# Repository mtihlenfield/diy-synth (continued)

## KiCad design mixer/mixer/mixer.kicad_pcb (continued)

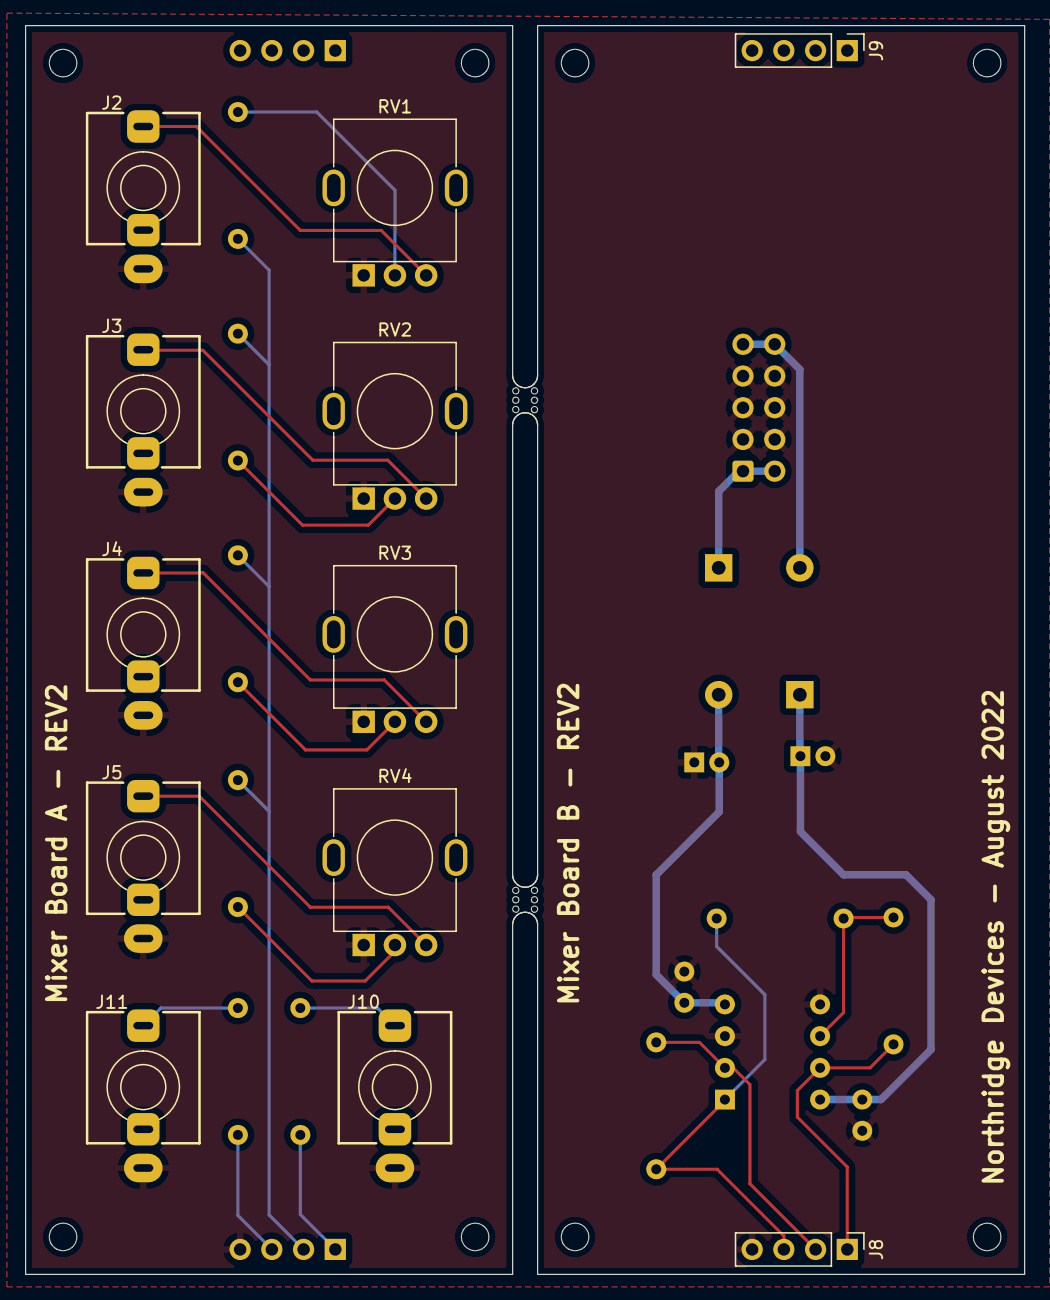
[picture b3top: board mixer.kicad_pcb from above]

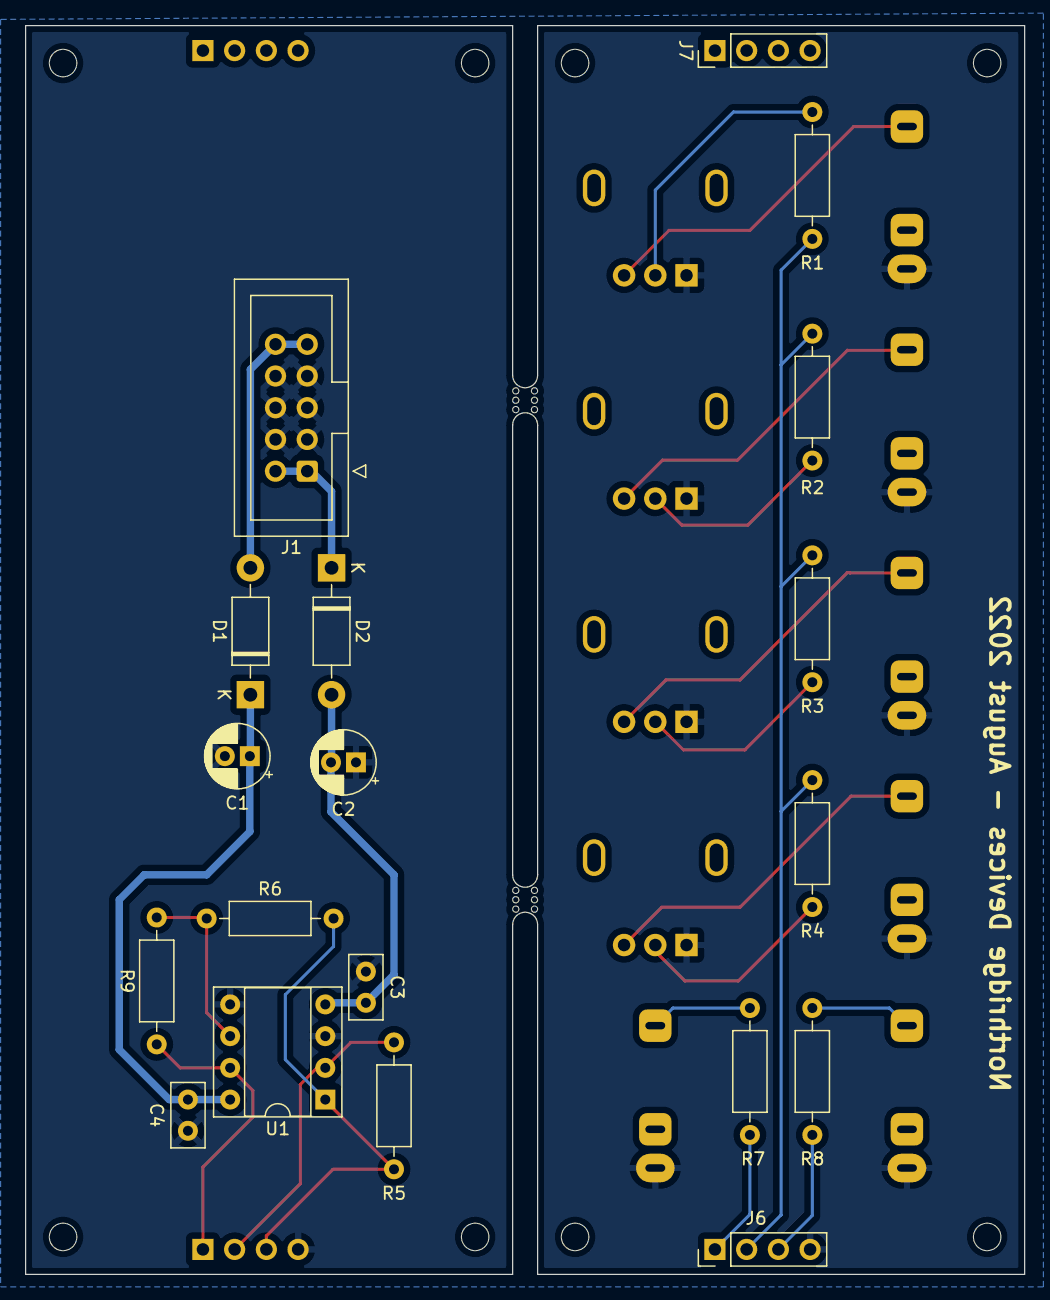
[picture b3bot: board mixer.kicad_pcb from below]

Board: 2 copper layers, 80.0 x 100.0 mm, 41 parts (19 on the bottom side), 22 nets.

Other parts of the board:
mouse-bite-2mm-slot, mouse-bite-2mm-slot#2: VAL**; mouse-bite-2mm-slot

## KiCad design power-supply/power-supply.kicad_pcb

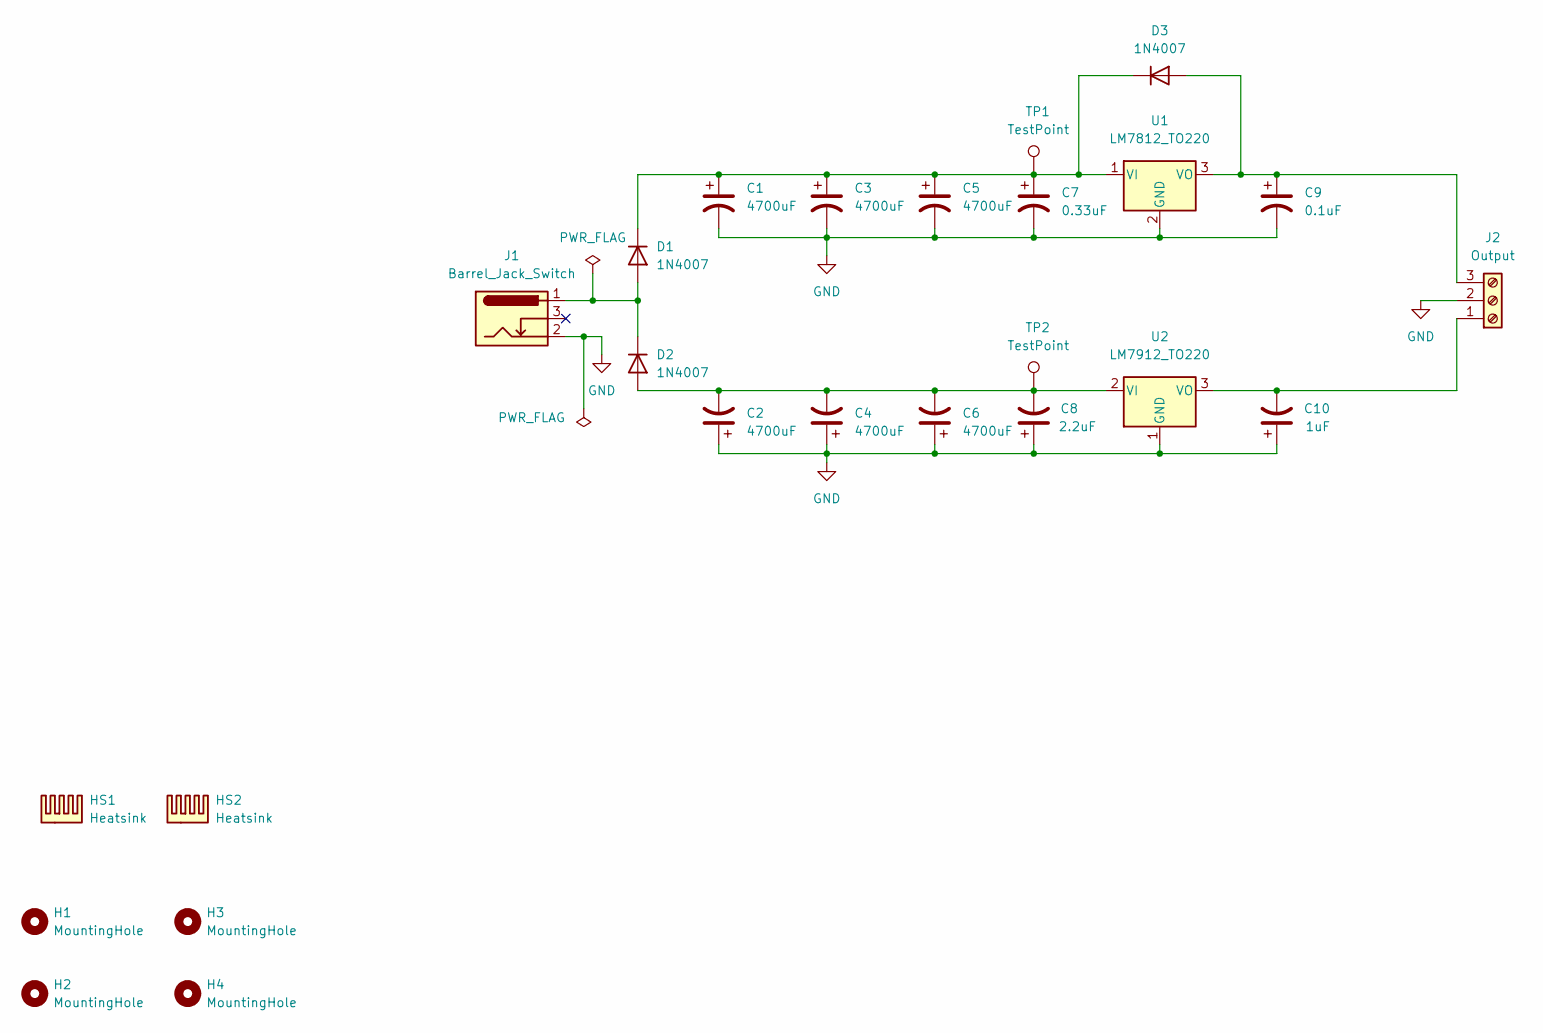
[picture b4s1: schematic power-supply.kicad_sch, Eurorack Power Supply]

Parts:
C1, C2, C3, C4, C5, C6: 4700uF; CP_Radial_D16.0mm_P7.50mm; Manufacturer Part No. JRB1E472M07501600250000B
C7: 0.33uF; CP_Radial_Tantal_D5.0mm_P2.50mm; Manufacturer Part No. 1uF 35V Radial Capacitor Tantalum
C8: 2.2uF; CP_Radial_Tantal_D5.0mm_P2.50mm; Manufacturer Part No. 1uF 35V Radial Capacitor Tantalum
C9: 0.1uF; CP_Radial_Tantal_D5.0mm_P2.50mm; Manufacturer Part No. 1uF 35V Radial Capacitor Tantalum
C10: 1uF; CP_Radial_Tantal_D5.0mm_P2.50mm; Manufacturer Part No. 1uF 35V Radial Capacitor Tantalum
D1, D2, D3: 1N4007; D_DO-41_SOD81_P10.16mm_Horizontal; Manufacturer Part No. 1N4007
H1, H2, H3, H4: MountingHole; MountingHole_3.2mm_M3
HS1, HS2: Heatsink; Manufacturer Part No. Tayda
J1: Barrel_Jack_Switch; BarrelJack_Horizontal_2.1mm_WEALTH_METAL; Manufacturer Part No. DC Power Jack 2.1mm
J2: Output; DG126; Manufacturer Part No. DG126-03P
TP1, TP2: TestPoint; TestPoint_Pad_D1.5mm
U1: LM7812_TO220; TO-220-3_Vertical; Manufacturer Part No. L7812CV
U2: LM7912_TO220; TO-220-3_Vertical; Manufacturer Part No. L7912CV

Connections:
GND: C1.2, C2.1, C3.2, C4.1, C5.2, C6.1, C7.2, C8.1, C9.2, C10.1, J1.2, J2.2, U1.2 (GND), U2.1 (GND)
unnamed: C1.1, C3.1, C5.1, C7.1, D1.1 (K), D3.1 (K), TP1.1, U1.1 (VI)
unnamed: C2.2, C4.2, C6.2, C8.2, D2.2 (A), TP2.1, U2.2 (VI)
unnamed: C9.1, D3.2 (A), J2.3, U1.3 (VO)
unnamed: C10.2, J2.1, U2.3 (VO)
unnamed: D1.2 (A), D2.1 (K), J1.1

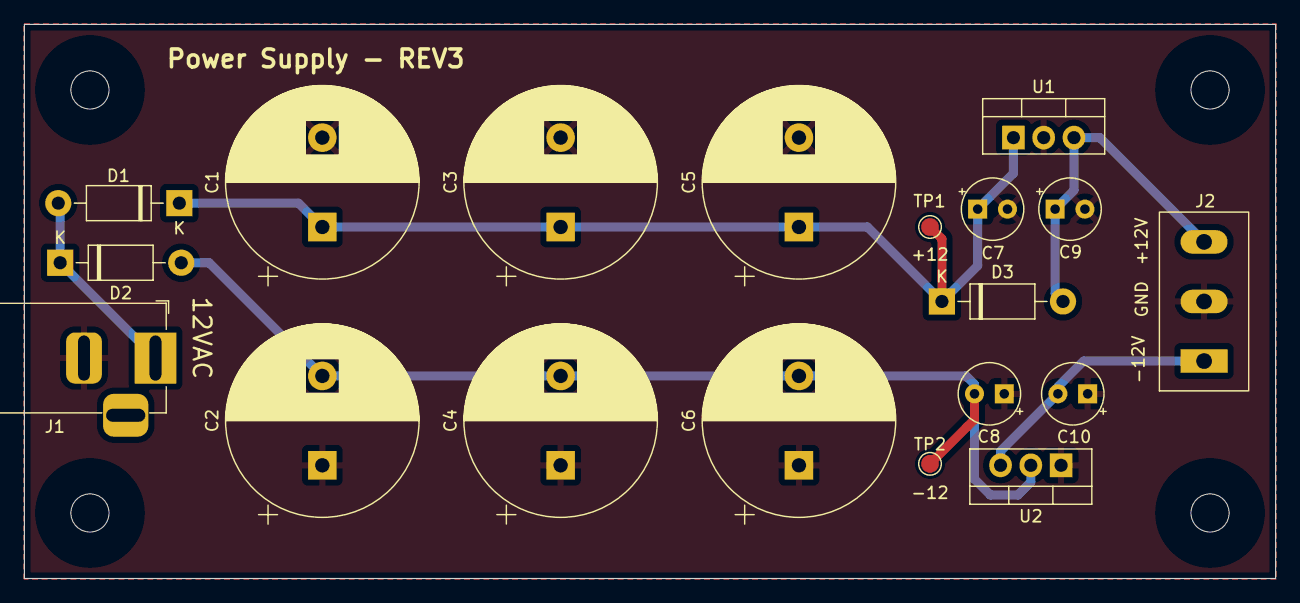
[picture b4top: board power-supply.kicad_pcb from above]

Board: 2 copper layers, 105.0 x 46.5 mm, 23 parts (0 on the bottom side), 6 nets.

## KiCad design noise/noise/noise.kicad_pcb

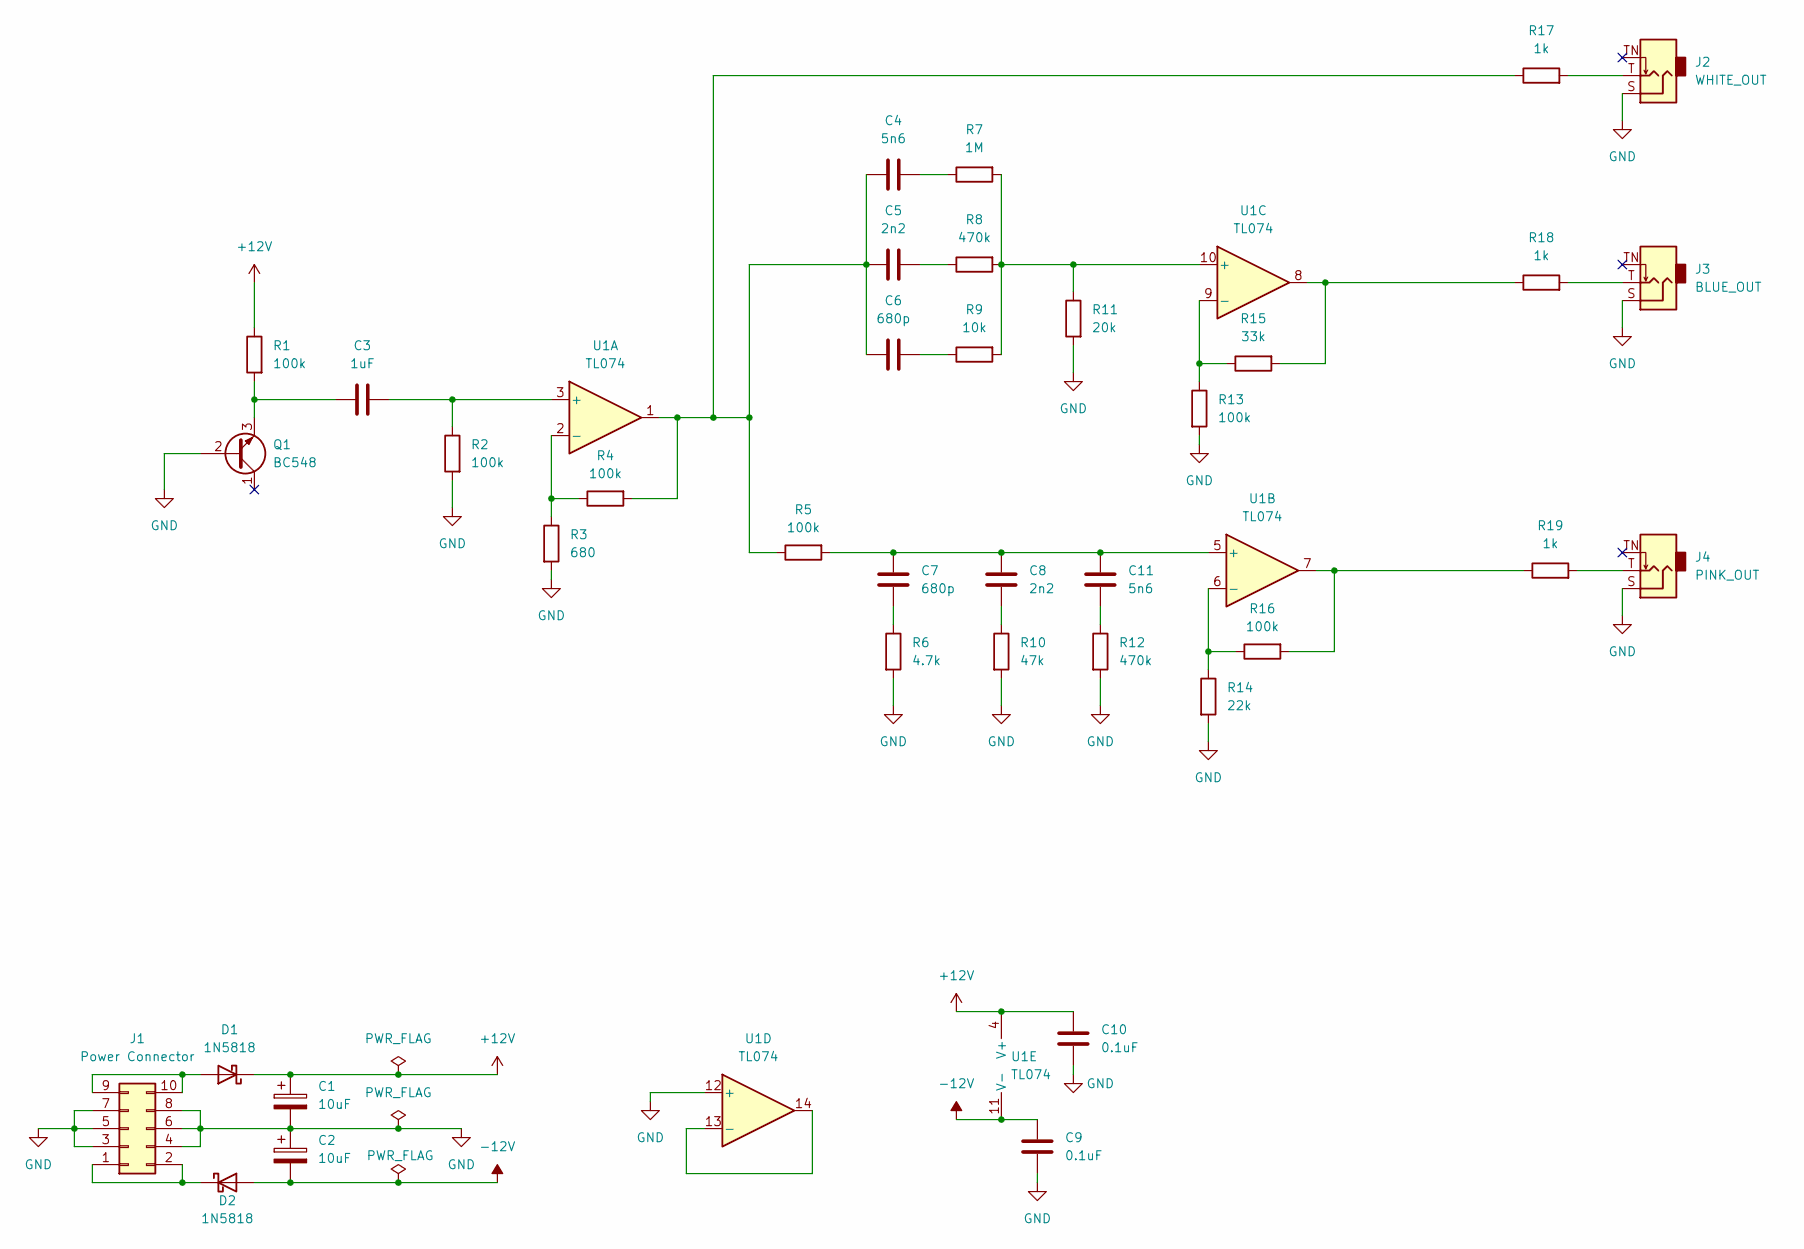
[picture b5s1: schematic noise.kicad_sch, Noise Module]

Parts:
C1, C2: 10uF; CP_Radial_D5.0mm_P2.00mm; Manufacturer Part No. WK1CM100D11OT
C3: 1uF; C_Rect_L7.2mm_W3.5mm_P5.00mm_FKS2_FKP2_MKS2_MKP2; Manufacturer Part No. MKS2B041001C00KSSD
C4, C11: 5n6; C_Rect_L7.2mm_W2.5mm_P5.00mm_FKS2_FKP2_MKS2_MKP2; Manufacturer Part No. 5.6nF/100V
C5, C8: 2n2; C_Rect_L7.2mm_W2.5mm_P5.00mm_FKS2_FKP2_MKS2_MKP2; Manufacturer Part No. FKS2D012201A00JSSD
C6, C7: 680p; C_Rect_L7.2mm_W5.5mm_P5.00mm_FKS2_FKP2_MKS2_MKP2; Manufacturer Part No. FKP2O106801G00JSSD
C9, C10: 0.1uF; C_Disc_D5.0mm_W2.5mm_P2.50mm; Manufacturer Part No. 0.1uF 50V Ceramic Disc Capacitor
D1, D2: 1N5818; D_DO-41_SOD81_P10.16mm_Horizontal; Manufacturer Part No. 1N5817
J1: Power Connector; IDC-Header_2x05_P2.54mm_Vertical; Manufacturer Part No. BHD10PHZT
J2: WHITE_OUT; PJ-323M; Manufacturer Part No. PJ-323M
J3: BLUE_OUT; PJ-323M; Manufacturer Part No. PJ-323M
J4: PINK_OUT; PJ-323M; Manufacturer Part No. PJ-323M
Q1: BC548; TO-92_Inline; Manufacturer Part No. BC548B
R1, R2, R4, R5, R13, R16: 100k; R_Axial_DIN0207_L6.3mm_D2.5mm_P10.16mm_Horizontal; Manufacturer Part No. MF0W4FF1003A50
R3: 680; R_Axial_DIN0207_L6.3mm_D2.5mm_P10.16mm_Horizontal; Manufacturer Part No. MF0W4FF6800A50
R6: 4.7k; R_Axial_DIN0207_L6.3mm_D2.5mm_P10.16mm_Horizontal; Manufacturer Part No. MF0W4FF4701A50
R7: 1M; R_Axial_DIN0207_L6.3mm_D2.5mm_P10.16mm_Horizontal; Manufacturer Part No. MF0W4FF1004A50
R8, R12: 470k; R_Axial_DIN0207_L6.3mm_D2.5mm_P10.16mm_Horizontal; Manufacturer Part No. MF0W4FF4703A50
R9: 10k; R_Axial_DIN0207_L6.3mm_D2.5mm_P10.16mm_Horizontal; Manufacturer Part No. MF0W4FF1002A50
R10: 47k; R_Axial_DIN0207_L6.3mm_D2.5mm_P10.16mm_Horizontal; Manufacturer Part No. MF0W4FF4702A50
R11: 20k; R_Axial_DIN0207_L6.3mm_D2.5mm_P10.16mm_Horizontal; Manufacturer Part No. MF0W4FF2002A50
R14: 22k; R_Axial_DIN0207_L6.3mm_D2.5mm_P10.16mm_Horizontal; Manufacturer Part No. MF0W4FF2202A50
R15: 33k; R_Axial_DIN0207_L6.3mm_D2.5mm_P10.16mm_Horizontal; Manufacturer Part No. MF0W4FF3302A50
R17, R18, R19: 1k; R_Axial_DIN0207_L6.3mm_D2.5mm_P10.16mm_Horizontal; Manufacturer Part No. MF0W4FF1001A50
U1: TL074; DIP-14_W7.62mm_Socket; Manufacturer Part No. TL074CN

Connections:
+12V: C1.1, C10.1, D1.1 (K), R1.1, U1.4 (V+)
-12V: C2.2, C9.1, D2.2 (A), U1.11 (V-)
GND: C1.2, C2.1, C9.2, C10.2, J1.3, J1.4, J1.5, J1.6, J1.7, J1.8, J2.S, J3.S, J4.S, Q1.2 (B), R2.2, R3.2, R6.2, R10.2, R11.2, R12.2, R13.2, R14.2, U1.12 (+)
unnamed: C3.1, Q1.3 (E), R1.2
unnamed: C3.2, R2.1, U1.3 (+)
unnamed: C4.1, C5.1, C6.1, R4.2, R5.1, R17.1, U1.1
unnamed: C4.2, R7.1
unnamed: C5.2, R8.1
unnamed: C6.2, R9.1
unnamed: C7.1, R6.1
unnamed: C8.1, R10.1
unnamed: C11.1, R12.1
unnamed: C7.2, C8.2, C11.2, R5.2, U1.5 (+)
unnamed: D1.2 (A), J1.9, J1.10
unnamed: D2.1 (K), J1.1, J1.2
unnamed: J2.T, R17.2
unnamed: J3.T, R18.2
unnamed: J4.T, R19.2
unnamed: R3.1, R4.1, U1.2 (-)
unnamed: R7.2, R8.2, R9.2, R11.1, U1.10 (+)
unnamed: R13.1, R15.1, U1.9 (-)
unnamed: R14.1, R16.1, U1.6 (-)
unnamed: R15.2, R18.1, U1.8
unnamed: R16.2, R19.1, U1.7
unnamed: U1.13 (-), U1.14

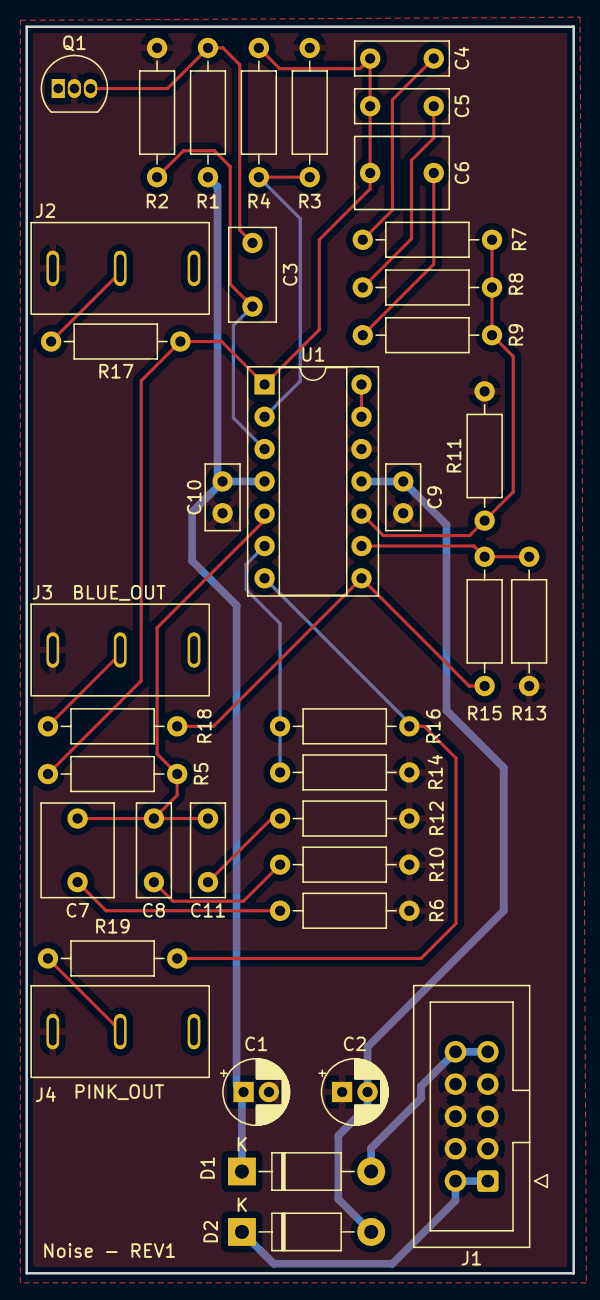
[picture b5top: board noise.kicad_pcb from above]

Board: 2 copper layers, 43.0 x 98.0 mm, 38 parts (0 on the bottom side), 25 nets.

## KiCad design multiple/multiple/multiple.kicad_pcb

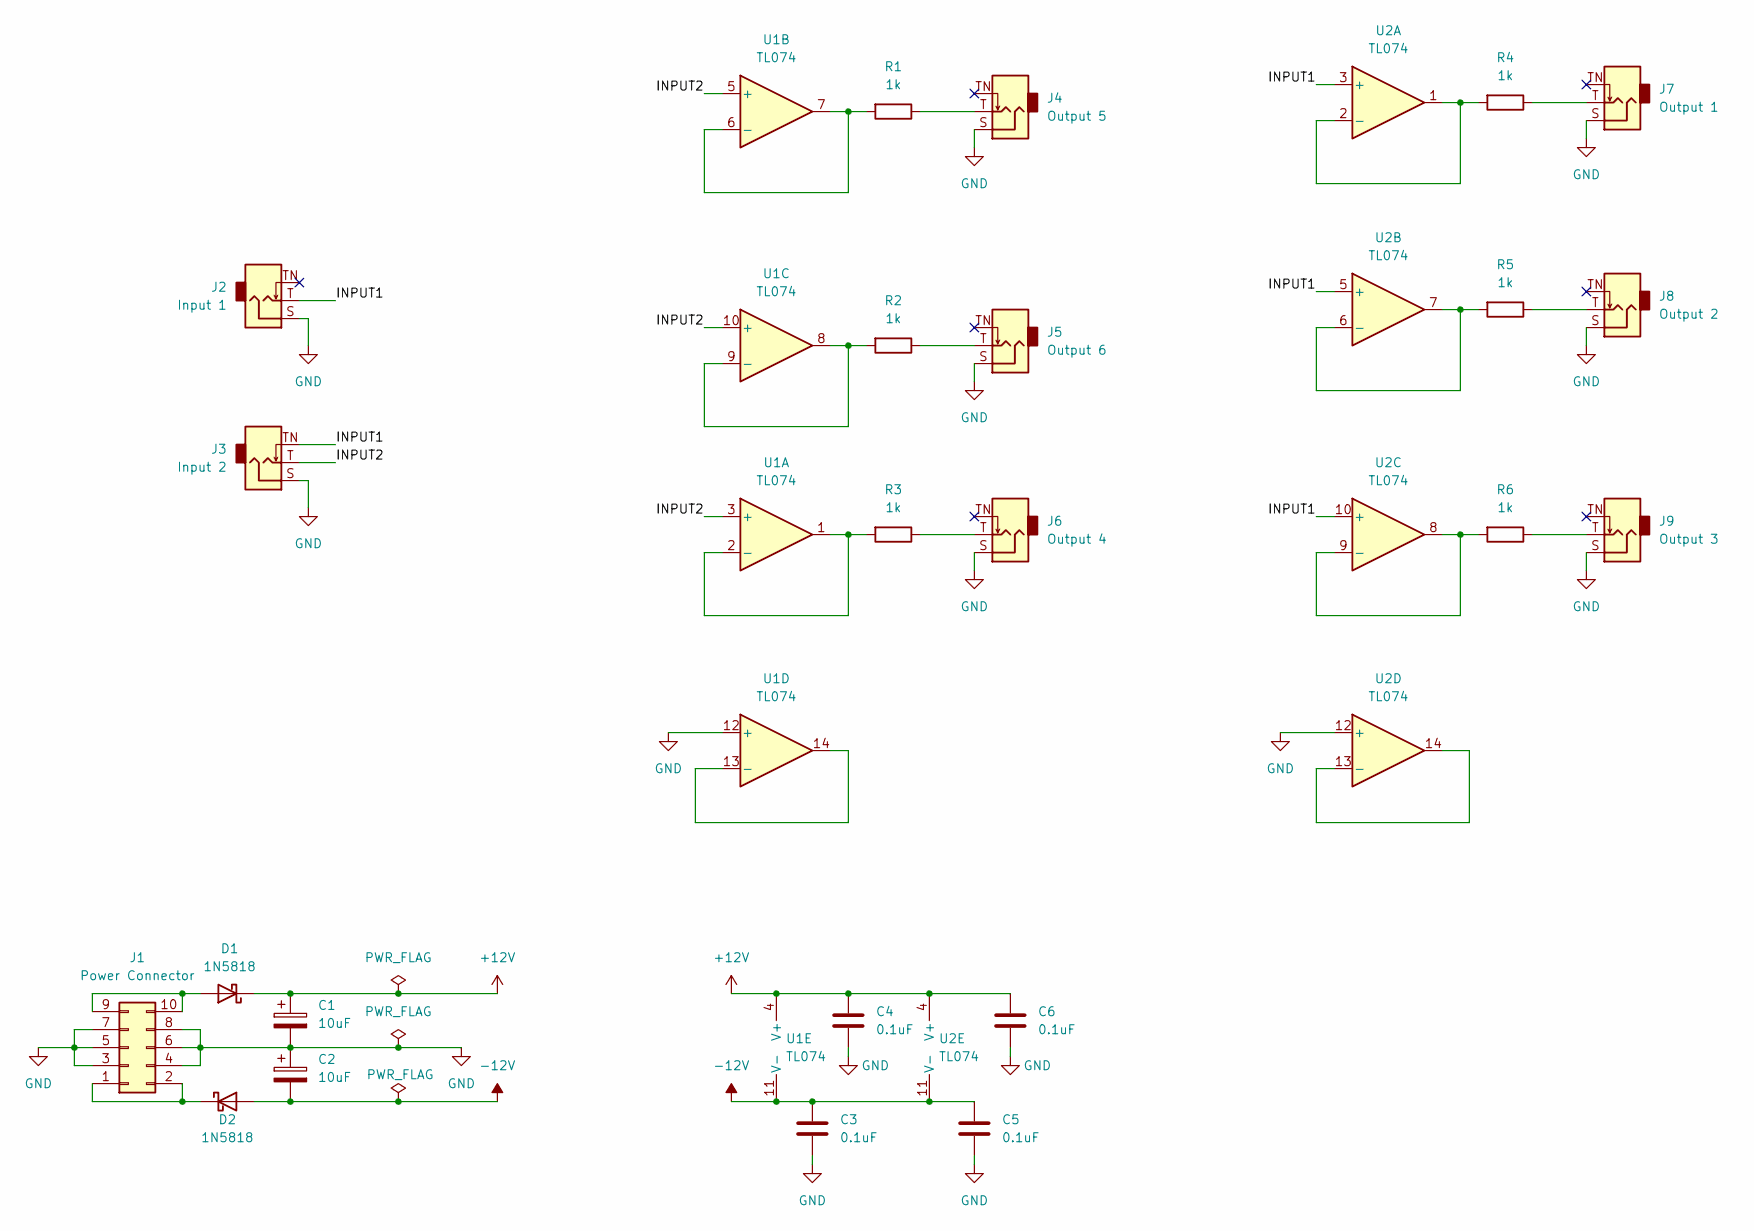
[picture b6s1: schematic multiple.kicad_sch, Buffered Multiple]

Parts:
C1, C2: 10uF; CP_Radial_D5.0mm_P2.00mm; Manufacturer Part No. WK1CM100D11OT
C3, C4, C5, C6: 0.1uF; C_Disc_D5.0mm_W2.5mm_P2.50mm; Manufacturer Part No. 0.1uF 50V Ceramic Disc Capacitor
D1, D2: 1N5818; D_DO-41_SOD81_P10.16mm_Horizontal; Manufacturer Part No. 1N5817
J1: Power Connector; IDC-Header_2x05_P2.54mm_Vertical; Manufacturer Part No. BHD10PHZT
J2: Input 1; PJ-323M; Manufacturer Part No. PJ-323M
J3: Input 2; PJ-323M; Manufacturer Part No. PJ-323M
J4: Output 5; PJ-323M; Manufacturer Part No. PJ-323M
J5: Output 6; PJ-323M; Manufacturer Part No. PJ-323M
J6: Output 4; PJ-323M; Manufacturer Part No. PJ-323M
J7: Output 1; PJ-323M; Manufacturer Part No. PJ-323M
J8: Output 2; PJ-323M; Manufacturer Part No. PJ-323M
J9: Output 3; PJ-323M; Manufacturer Part No. PJ-323M
R1, R2, R3, R4, R5, R6: 1k; R_Axial_DIN0207_L6.3mm_D2.5mm_P10.16mm_Horizontal; Manufacturer Part No. MF0W4FF1001A50
U1, U2: TL074; DIP-14_W7.62mm_Socket; Manufacturer Part No. TL074CN

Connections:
+12V: C1.1, C4.1, C6.1, D1.1 (K), U1.4 (V+), U2.4 (V+)
-12V: C2.2, C3.1, C5.1, D2.2 (A), U1.11 (V-), U2.11 (V-)
/INPUT1: J2.T, J3.TN, U2.3 (+), U2.5 (+), U2.10 (+)
/INPUT2: J3.T, U1.3 (+), U1.5 (+), U1.10 (+)
GND: C1.2, C2.1, C3.2, C4.2, C5.2, C6.2, J1.3, J1.4, J1.5, J1.6, J1.7, J1.8, J2.S, J3.S, J4.S, J5.S, J6.S, J7.S, J8.S, J9.S, U1.12 (+), U2.12 (+)
unnamed: D1.2 (A), J1.9, J1.10
unnamed: D2.1 (K), J1.1, J1.2
unnamed: J4.T, R1.1
unnamed: J5.T, R2.1
unnamed: J6.T, R3.1
unnamed: J7.T, R4.1
unnamed: J8.T, R5.1
unnamed: J9.T, R6.1
unnamed: R1.2, U1.6 (-), U1.7
unnamed: R2.2, U1.8, U1.9 (-)
unnamed: R3.2, U1.1, U1.2 (-)
unnamed: R4.2, U2.1, U2.2 (-)
unnamed: R5.2, U2.6 (-), U2.7
unnamed: R6.2, U2.8, U2.9 (-)
unnamed: U1.13 (-), U1.14
unnamed: U2.13 (-), U2.14

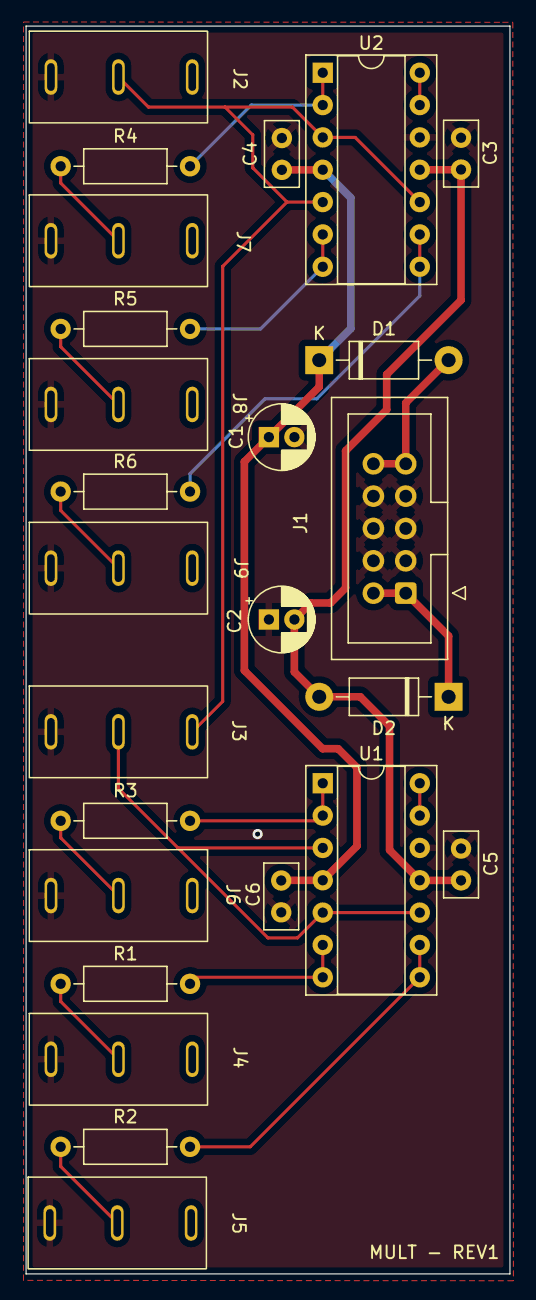
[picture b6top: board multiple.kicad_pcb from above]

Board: 2 copper layers, 38.0 x 98.0 mm, 25 parts (0 on the bottom side), 21 nets.

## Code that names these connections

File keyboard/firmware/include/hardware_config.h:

#ifndef __HARDWARE_CONFIG_H__
#define __HARDWARE_CONFIG_H__

#define SER_CLK 1 // GPIO1 - PIN 2
#define SER_DATA 0 // GPIO0 - PIN 1

#define OCTAVE_DOWN_LED_PIN 15 // GPIO15 - PIN 20
#define OCTAVE_MID_LED_PIN 14 // GPIO15 - PIN 19
#define OCTAVE_UP_LED_PIN 13 // GPIO15 - PIN 17

#define DAC_SPI_PORT spi1
#define DAC_PIN_CS 9 // GP9
#define DAC_PIN_SCK 10 // GP10
#define DAC_PIN_MOSI 11 // GP11
#define DAC_REFV 2.5 // Using a TL431 in it's default state
#define DAC_CLK_SPEED (1000 * 1000) // 1Mhz

// Amount of gain applied to the CV signal by our op-amp
// configuration.
#define CV_OPAMP_GAIN 3.2

#define GATE_OUT_PIN 5 // GP5

#define PWR_LED_PIN 25 // GP25
#define LED1_PIN 15 // GP15
#define LED2_PIN 14 // GP14
#define LED3_PIN 13 // GP13

#define SHIFT_REG_CLK_PIN 17 // GPIO17 - PIN 22
#define SHIFT_REG_DATA_PIN 16 // GPIO16 - PIN 21

// Total number of shift register outputs
#define SHIFT_REG_OUTPUTS 16

// NOTE rows are held high,
#define MATRIX_ROWS 6
#define MATRIX_COLS 10
#define MATRIX_R1_PIN 26 // GPIO26 - PIN 31
#define MATRIX_R2_PIN 22 // GPIO22 - PIN 29
#define MATRIX_R3_PIN 21 // GPIO21 - PIN 27
#define MATRIX_R4_PIN 20 // GPIO20 - PIN 26
#define MATRIX_R5_PIN 19 // GPIO19 - PIN 25
#define MATRIX_R6_PIN 18 // GPIO18 - PIN 24
#define NUM_MATRIX_KEYS (MATRIX_ROWS * MATRIX_COLS)

#endif

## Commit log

2022-08-20 Initial monorepo commit
2022-08-20 Updated mixer and multiple to use new common libs
2022-08-20 Updated power supply to use new common libs
2022-08-20 Partially converted keyboard libaries over to common dir
2022-08-20 started noise module
2022-08-21 Added footprints for noise module parts and created BOM
2022-08-21 Completed noise panel. Started on noise PCB
2022-08-21 Completed noise pcb
2022-08-21 Added more text to noise pcb
2022-08-21 Generated final versions of noise pcb and panel
2022-08-24 Added 4HP panel to eurolibs
2022-08-28 Fixed capacitor polarity on power supply
2022-08-28 Started sample and hold
2022-09-17 Added rev2 of mixer. Fixed opamp configuation and panel connector layout
2022-09-17 Updated graphics on rev2 mixer panel
2022-09-17 Updated graphics on rev2 multiple panel
2022-09-17 Added 2HP panel footprint
2022-09-19 Added REV1 of sample and hold board/panel
2022-09-19 Added revision text to sample and hold board/panel
2022-10-27 Converted noise to use 2n3904
2023-12-09 Simplified keyboard for rev1
2023-12-09 Removed unwanted dirs
2023-12-11 Finalized keyboard controller rev1 board
2024-01-04 Started on case 3d model for keyboard
2024-01-04 Removed unwanted files
2024-01-08 Completed 3d model for keyboard pcb
2024-01-08 Added power polarity symbol to keyboard pcb
2024-01-10 Fixes to keyboard controller rev1
2024-01-10 Updated keyboard firmware to account for new pin layout
2024-01-11 Updated octave shift handling code for keyboard
2024-01-11 Fixed wiring of keyboard connector, added TODOs
2024-01-12 keyboard firmare update to fix negative CV output
2024-01-13 Completed keyboard controller rev2
2024-01-13 Added more screw holes to keybed model
2024-01-18 Removed old vco
2024-01-18 started on lfo module
2024-02-11 Updated keyboard controller bom
2024-06-21 Added super basic midi output to keyboard
